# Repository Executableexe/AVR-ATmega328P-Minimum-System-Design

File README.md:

# AVR-ATmega328P-Minimum-System-Design
PCB design using KiKad for the submission of task 1

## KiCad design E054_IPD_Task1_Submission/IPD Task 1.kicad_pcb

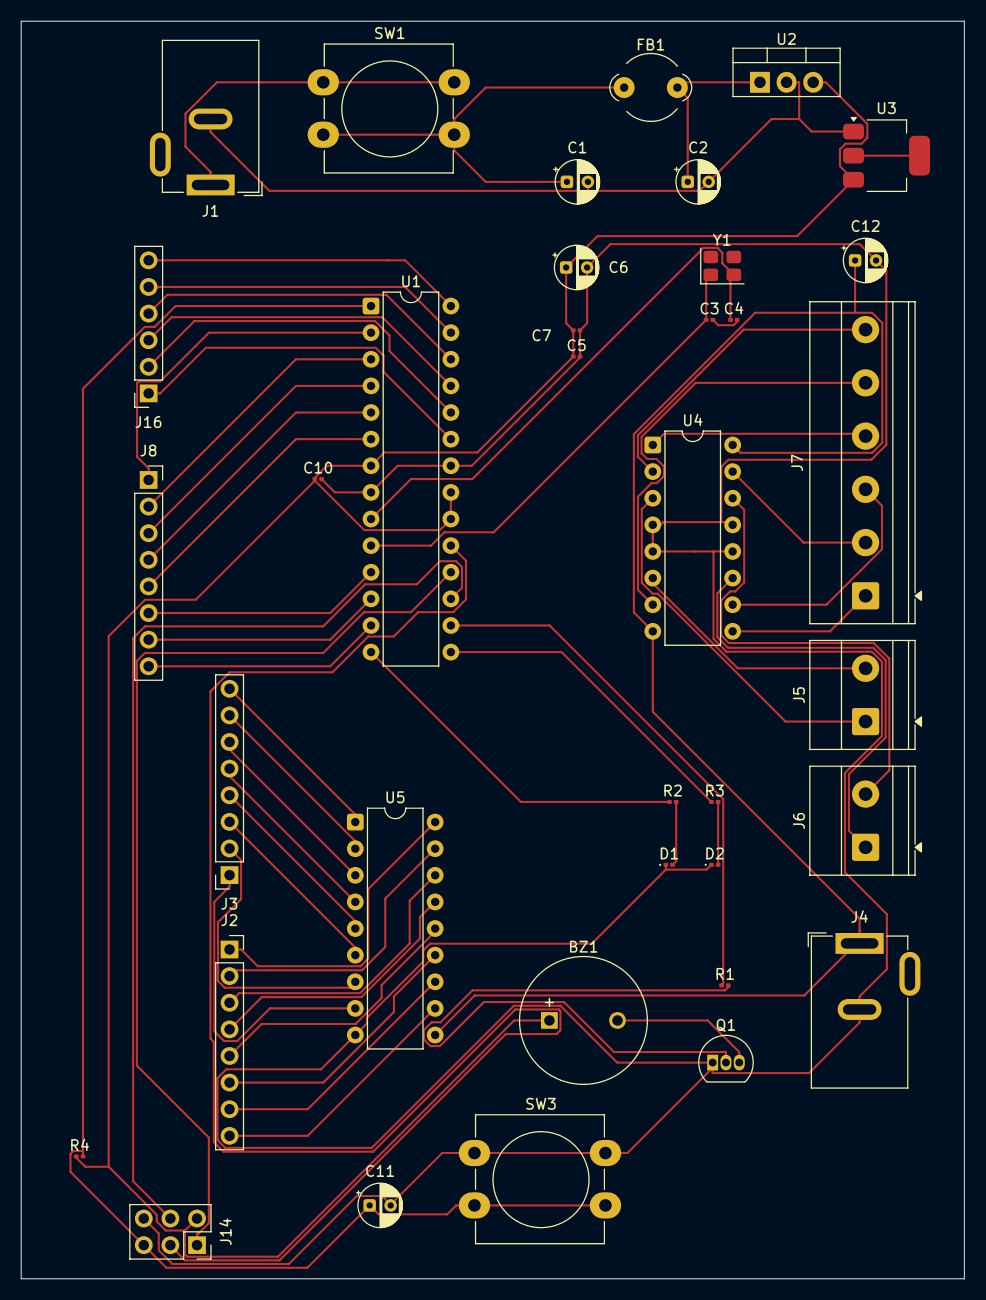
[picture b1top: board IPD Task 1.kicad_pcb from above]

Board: 2 copper layers, 90.0 x 120.0 mm, 37 parts (0 on the bottom side), 61 nets.

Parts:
BZ1: Buzzer; MagneticBuzzer_ProSignal_ABT-410-RC
C1, C2: 1u; CP_Radial_D4.0mm_P2.00mm
C3, C4: 22pf; C_0201_0603Metric
C5, C7: 100nf; C_0201_0603Metric
C6: 10uf; CP_Radial_D4.0mm_P2.00mm
C10: C; C_0201_0603Metric
C11: 1uf; CP_Radial_D4.0mm_P2.00mm
C12: 100uf; CP_Radial_D4.0mm_P2.00mm
D1, D2: LED; LED_0201_0603Metric
FB1: FerriteBead; LairdTech_28C0236-0JW-10
J1, J4: Barrel_Jack; BarrelJack_GCT_DCJ200-10-A_Horizontal
J2, J3, J8: Conn_01x08; PinSocket_1x08_P2.54mm_Vertical
J5, J6: TerminalBlock_Phoenix_MKDS-1,5-2-5.08_1x02_P5.08mm_Horizont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
J7: TerminalBlock_Phoenix_MKDS-1,5-6-5.08_1x06_P5.08mm_Horizont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
J14: Conn_02x03_Odd_Even; PinSocket_2x03_P2.54mm_Vertical
J16: Conn_01x06; PinSocket_1x06_P2.54mm_Vertical
Q1: 2N7000; TO-92_Inline
R1, R2, R3, R4: R; R_0201_0603Metric
SW1: Push to lock switch; SW_PUSH-12mm_Wuerth-430476085716
SW3: Push to ON Switch ( momentary ); SW_PUSH-12mm_Wuerth-430476085716
U1: ATmega328P-P; DIP-28_W7.62mm
U2: L7805; TO-220-3_Vertical
U3: AMS1117-3.3; SOT-223-3_TabPin2
U4: L293; DIP-16_W7.62mm
U5: ULN2803A; DIP-18_W7.62mm
Y1: Crystal; Crystal_SMD_Abracon_ABM8G-4Pin_3.2x2.5mm

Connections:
5V: BZ1.1 (+), C5.1, C6.1, C7.1, C10.1, J14.2, R4.1, U1.7 (VCC), U1.20 (AVCC), U1.21 (AREF), U2.3 (OUT), U3.3 (VI)
12V: C12.1, J4.1, U4.8 (VCC2), U4.16 (VCC1), U5.10 (COM)
GND: C5.2, C6.2, C7.2, C10.2, C11.2, C12.2, D1.1 (K), D2.1 (K), J4.2, J14.6, Q1.1 (S), SW3.1, U1.8 (GND), U1.22 (GND), U4.4 (GND), U4.5 (GND), U4.12 (GND), U4.13 (GND), U5.9 (GND)
GPIO_FGAG_2: R3.1, U1.15 (PB1)
GPIO_FLAG_1: R2.1, U1.14 (PB0)
MISO: J14.1, U1.18 (PB4)
MOSI: J14.4, U1.17 (PB3)
unnamed: BZ1.2 (-), Q1.3 (D)
unnamed: C1.1, FB1.1, SW1.2
unnamed: C3.2, C4.2
unnamed: D1.2 (A), R2.2
unnamed: D2.2 (A), R3.2
unnamed: J1.1, SW1.1
unnamed: J2.1, U5.18 (O1)
unnamed: J2.2, U5.17 (O2)
unnamed: J2.3, U5.16 (O3)
unnamed: J2.4, U5.15 (O4)
unnamed: J2.5, U5.14 (O5)
unnamed: J2.6, U5.13 (O6)
unnamed: J2.7, U5.12 (O7)
unnamed: J2.8, U5.11 (O8)
unnamed: J3.1, U5.8 (I8)
unnamed: J3.2, U5.7 (I7)
unnamed: J3.3, U5.6 (I6)
unnamed: J3.4, U5.5 (I5)
unnamed: J3.5, U5.4 (I4)
unnamed: J3.6, U5.3 (I3)
unnamed: J3.7, U5.2 (I2)
unnamed: J3.8, U5.1 (I1)
unnamed: J5.1, U4.3 (1Y)
unnamed: J5.2, U4.6 (2Y)
unnamed: J6.1, U4.11 (3Y)
unnamed: J6.2, U4.14 (4Y)
unnamed: J7.1, U4.9 (EN3,4)
unnamed: J7.2, U4.15 (4A)
unnamed: J7.3, U4.10 (3A)
unnamed: J7.4, U4.1 (EN1,2)
unnamed: J7.5, U4.7 (2A)
unnamed: J7.6, U4.2 (1A)
unnamed: J8.1, U1.2 (PD0)
unnamed: J8.2, U1.3 (PD1)
unnamed: J8.3, U1.4 (PD2)
unnamed: J8.4, U1.5 (PD3)
unnamed: J8.5, U1.6 (PD4)
unnamed: J8.6, U1.11 (PD5)
unnamed: J8.7, U1.12 (PD6)
unnamed: J8.8, U1.13 (PD7)
unnamed: J16.1, U1.23 (PC0)
unnamed: J16.2, U1.24 (PC1)
unnamed: J16.3, U1.25 (PC2)
unnamed: J16.4, U1.26 (PC3)
unnamed: J16.5, U1.27 (PC4)
unnamed: J16.6, U1.28 (PC5)
unnamed: Q1.2 (G), R1.2
unnamed: C4.1, U1.9 (XTAL1/PB6), Y1.2
unnamed: C3.1, U1.10 (XTAL2/PB7), Y1.1
unnamed: C1.2, C2.2, J1.2, U2.2 (GND), U3.1 (GND)
unnamed: C2.1, FB1.2, U2.1 (IN)
PWM1: R1.1, U1.16 (PB2)
Reset: C11.1, J14.5, R4.2, SW3.2, U1.1 (~RESET/PC6)
SCK: J14.3, U1.19 (PB5)

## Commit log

2026-03-01 Create E054_IPD_Task1_Submission
2026-03-01 Added files for submission
